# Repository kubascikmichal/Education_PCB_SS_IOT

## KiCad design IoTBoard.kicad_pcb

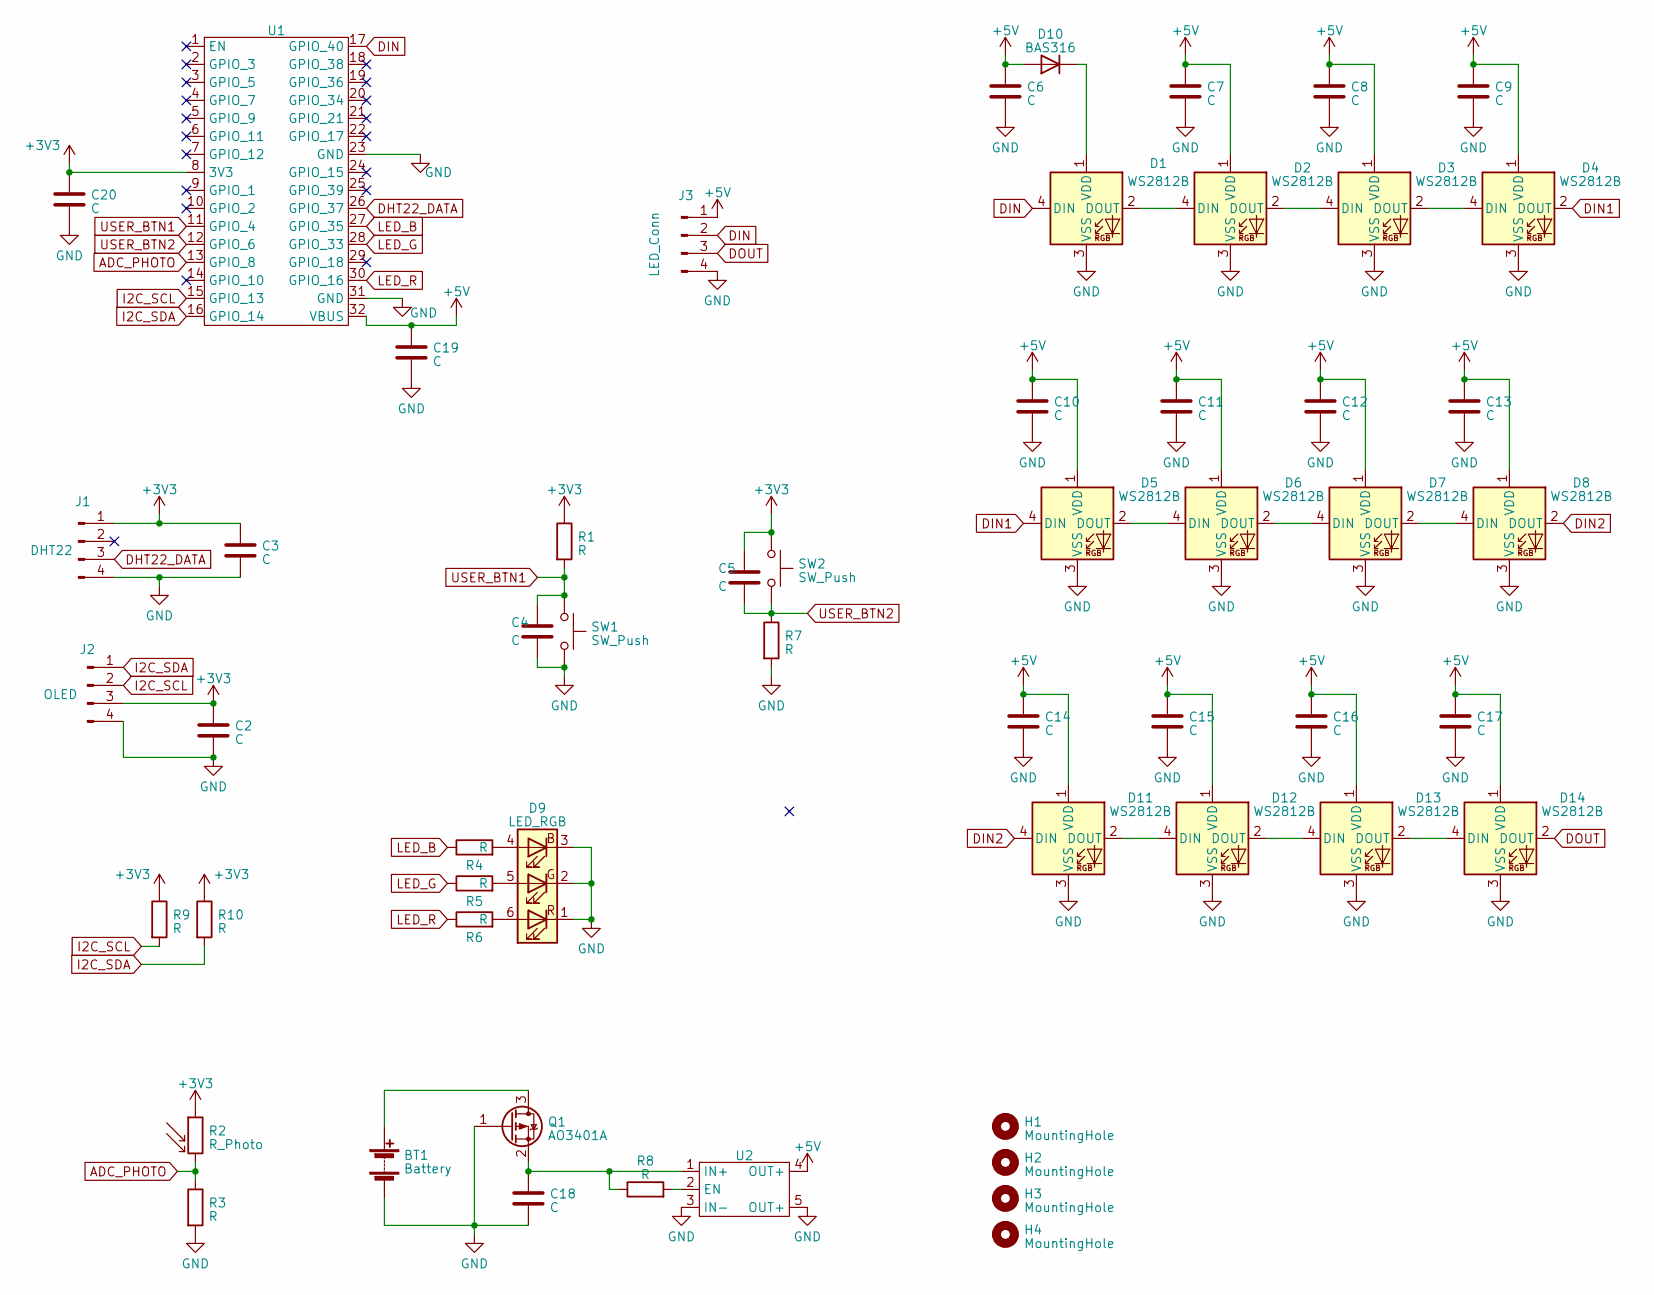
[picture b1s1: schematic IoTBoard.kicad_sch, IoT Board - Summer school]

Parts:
BT1: Battery; BatteryHolder_Keystone_2479_3xAAA
C2, C3, C4, C5, C6, C7, C8, C9, C10, C11, C12, C13, C14, C15, C16, C17, C18, C19, C20: C; C_0805_2012Metric
D1, D2, D3, D4, D5, D6, D7, D8, D11, D12, D13, D14: WS2812B; LED_WS2812B_PLCC4_5.0x5.0mm_P3.2mm
D9: LED_RGB; LED_Avago_PLCC6_3x2.8mm
D10: BAS316; D_SOD-323_HandSoldering
H1, H2, H3, H4: MountingHole; MountingHole_2.2mm_M2
J1: DHT22; PinHeader_1x04_P2.54mm_Vertical
J2: OLED; PinHeader_1x04_P2.54mm_Vertical
J3: LED_Conn; PinHeader_1x04_P2.54mm_Vertical
Q1: AO3401A; SOT-23
R1, R3, R4, R5, R6, R7, R8, R9, R10: R; R_0805_2012Metric
R2: R_Photo; R_LDR_4.9x4.2mm_P2.54mm_Vertical
SW1, SW2: SW_Push; SW_Push_1P1T_NO_6x6mm_H9.5mm
U1: WEMOS_S2_mini_traced
U2: BuckBoost5V

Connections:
+3V3: C2.1, C3.1, C5.1, C20.1, J1.1, J2.3, R1.1, R2.1, R9.1, R10.1, SW2.1, U1.8 (3V3)
+5V: C6.1, C7.1, C8.1, C9.1, C10.1, C11.1, C12.1, C13.1, C14.1, C15.1, C16.1, C17.1, C19.1, D2.1 (VDD), D3.1 (VDD), D4.1 (VDD), D5.1 (VDD), D6.1 (VDD), D7.1 (VDD), D8.1 (VDD), D10.2 (A), D11.1 (VDD), D12.1 (VDD), D13.1 (VDD), D14.1 (VDD), J3.1, U1.32 (VBUS), U2.4 (OUT+)
ADC_PHOTO: R2.2, R3.1, U1.13 (GPIO_8)
DHT22_DATA: J1.3, U1.26 (GPIO_37)
DIN: D1.4 (DIN), J3.2, U1.17 (GPIO_40)
DIN1: D4.2 (DOUT), D5.4 (DIN)
DIN2: D8.2 (DOUT), D11.4 (DIN)
DOUT: D14.2 (DOUT), J3.3
GND: BT1.2 (-), C2.2, C3.2, C4.2, C6.2, C7.2, C8.2, C9.2, C10.2, C11.2, C12.2, C13.2, C14.2, C15.2, C16.2, C17.2, C18.2, C19.2, C20.2, D1.3 (VSS), D2.3 (VSS), D3.3 (VSS), D4.3 (VSS), D5.3 (VSS), D6.3 (VSS), D7.3 (VSS), D8.3 (VSS), D9.1 (RK), D9.2 (GK), D9.3 (BK), D11.3 (VSS), D12.3 (VSS), D13.3 (VSS), D14.3 (VSS), J1.4, J2.4, J3.4, Q1.1 (G), R3.2, R7.2, SW1.2, U1.23 (GND), U1.31 (GND), U2.3 (IN-), U2.5 (OUT+)
I2C_SCL: J2.2, R9.2, U1.15 (GPIO_13)
I2C_SDA: J2.1, R10.2, U1.16 (GPIO_14)
LED_B: R4.1, U1.27 (GPIO_35)
LED_G: R5.1, U1.28 (GPIO_33)
LED_R: R6.1, U1.30 (GPIO_16)
unnamed: BT1.1 (+), Q1.3 (D)
unnamed: D1.2 (DOUT), D2.4 (DIN)
unnamed: D1.1 (VDD), D10.1 (K)
unnamed: D2.2 (DOUT), D3.4 (DIN)
unnamed: D3.2 (DOUT), D4.4 (DIN)
unnamed: D5.2 (DOUT), D6.4 (DIN)
unnamed: D6.2 (DOUT), D7.4 (DIN)
unnamed: D7.2 (DOUT), D8.4 (DIN)
unnamed: D9.4 (BA), R4.2
unnamed: D9.5 (GA), R5.2
unnamed: D9.6 (RA), R6.2
unnamed: D11.2 (DOUT), D12.4 (DIN)
unnamed: D12.2 (DOUT), D13.4 (DIN)
unnamed: D13.2 (DOUT), D14.4 (DIN)
unnamed: C18.1, Q1.2 (S), R8.1, U2.1 (IN+)
unnamed: R8.2, U2.2 (EN)
USER_BTN1: C4.1, R1.2, SW1.1, U1.11 (GPIO_4)
USER_BTN2: C5.2, R7.1, SW2.2, U1.12 (GPIO_6)

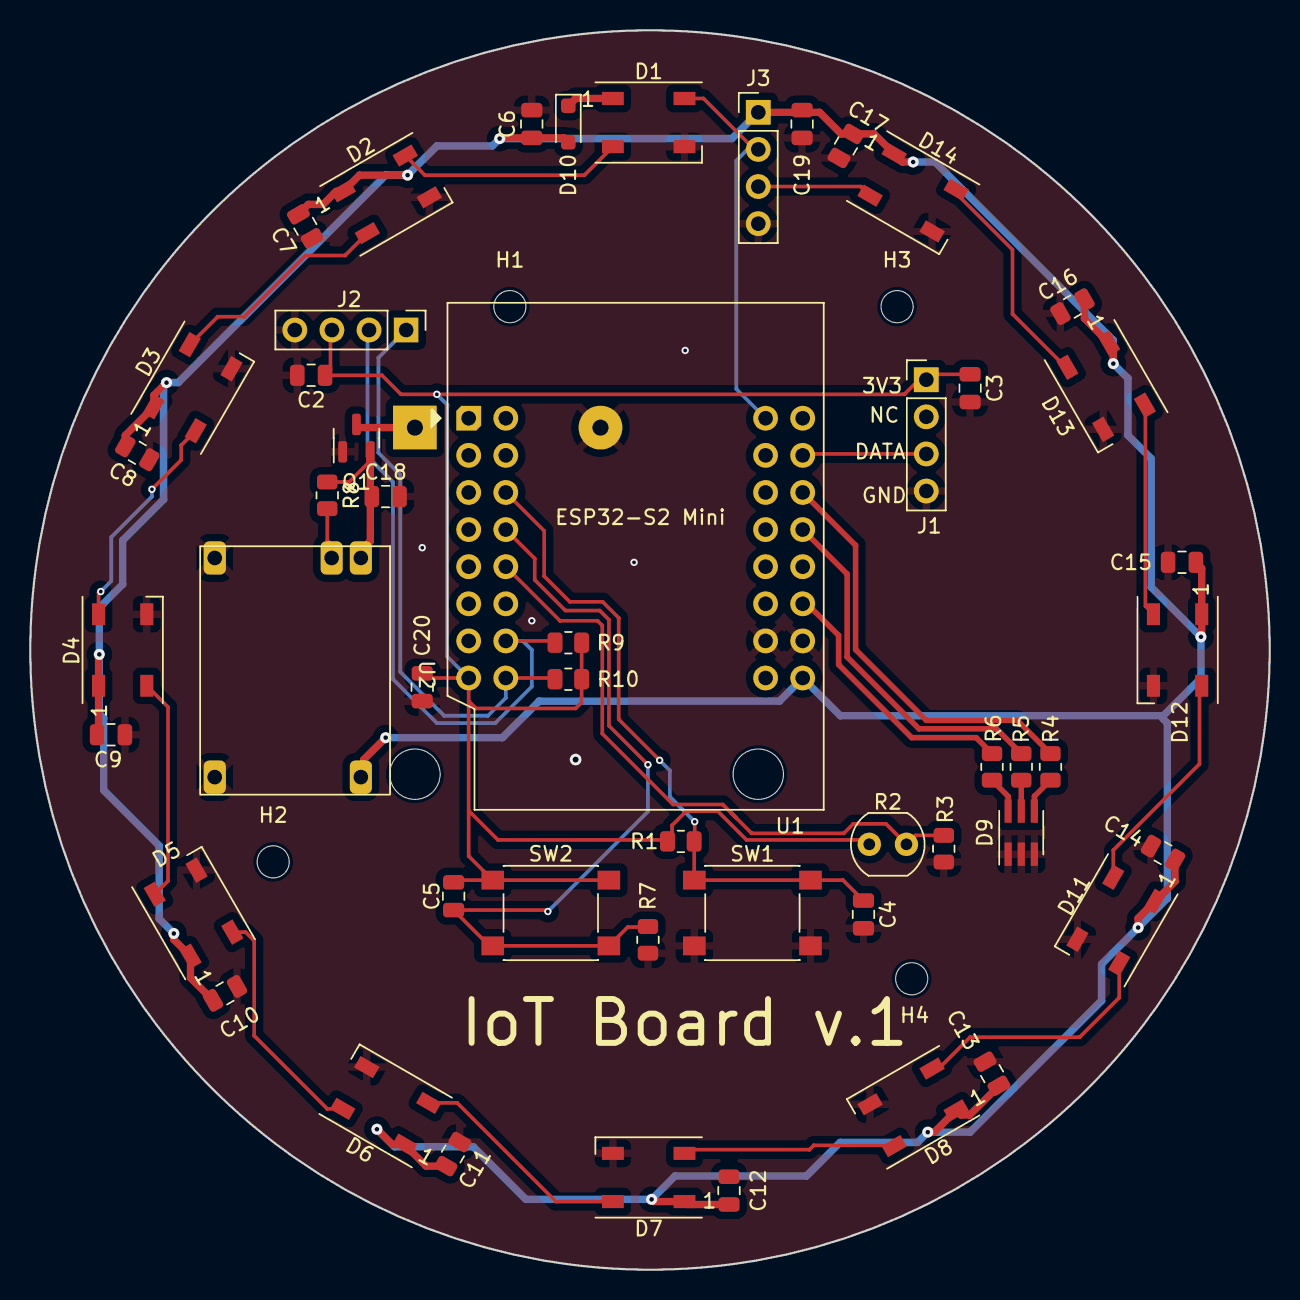
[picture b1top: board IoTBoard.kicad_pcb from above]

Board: 2 copper layers, 84.8 x 84.8 mm, 56 parts (1 on the bottom side), 32 nets.

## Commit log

2024-07-25 init
2024-09-26 Changed PCB
    Fixed errors
